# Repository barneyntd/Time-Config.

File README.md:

Time & Config.
==============

Time & Config. is a project to add a real-time clock and a configuration memory to a BBC microcomputer model B, giving
it some of the features of the BBC master. It has three main parts:
1.  A PCB containing a PCF2123 RTC, an FM25040B FRAM and an LTC4054 Li charger.
	This is designed to share a user port with a turbo-MMC card, but can also be used alone.
2.  A sideways ROM which implements:
	- OSBYTE 161 & 162: read and write NVRAM
	- OSWORD 14 & 15: read and set real-time clock
	- ROM service calls 40 & 41: extendable CONFIGURE & STATUS
	- \*-commands: TIME, CONFIGURE, STATUS, UNPLUG, INSERT & ROMS
	- configure terms: BAUD, BOOT, NOBOOT, CAPS, NOCAPS, SHCAPS, DATA, DELAY, FDRIVE, FILE, IGNORE, LANG, LOUD, QUIET, MODE, TUBE, NOTUBE, PRINT, REPEAT, TV
 	- help terms: T&C and TIME
3.  A version of SNTP over serial which allows you to synchronise the clock to internet time, to a precision of a few centiseconds.

#### Project folders
- **kicad** This holds the schematic and pcb design, as a kicad project;
- **ROM** This holds the source for the ROM code, in beebasm format;
- **sntp** This holds the SNTPoS client program in BASIC (without line numbers) and the sntpos\_server program in POSIX C.

#### Licence
This project is licensed under creative commons licence [CC BY-NC-SA 4.0](https://creativecommons.org/licenses/by-nc-sa/4.0/).
This means that you are free to use it for any noncommercial purpose, provided you credit the copyright holder, and pass on the same conditions.
If you want to create a commercial product based on Time & Config., you must obtain a seperate licence from the copyright holder.

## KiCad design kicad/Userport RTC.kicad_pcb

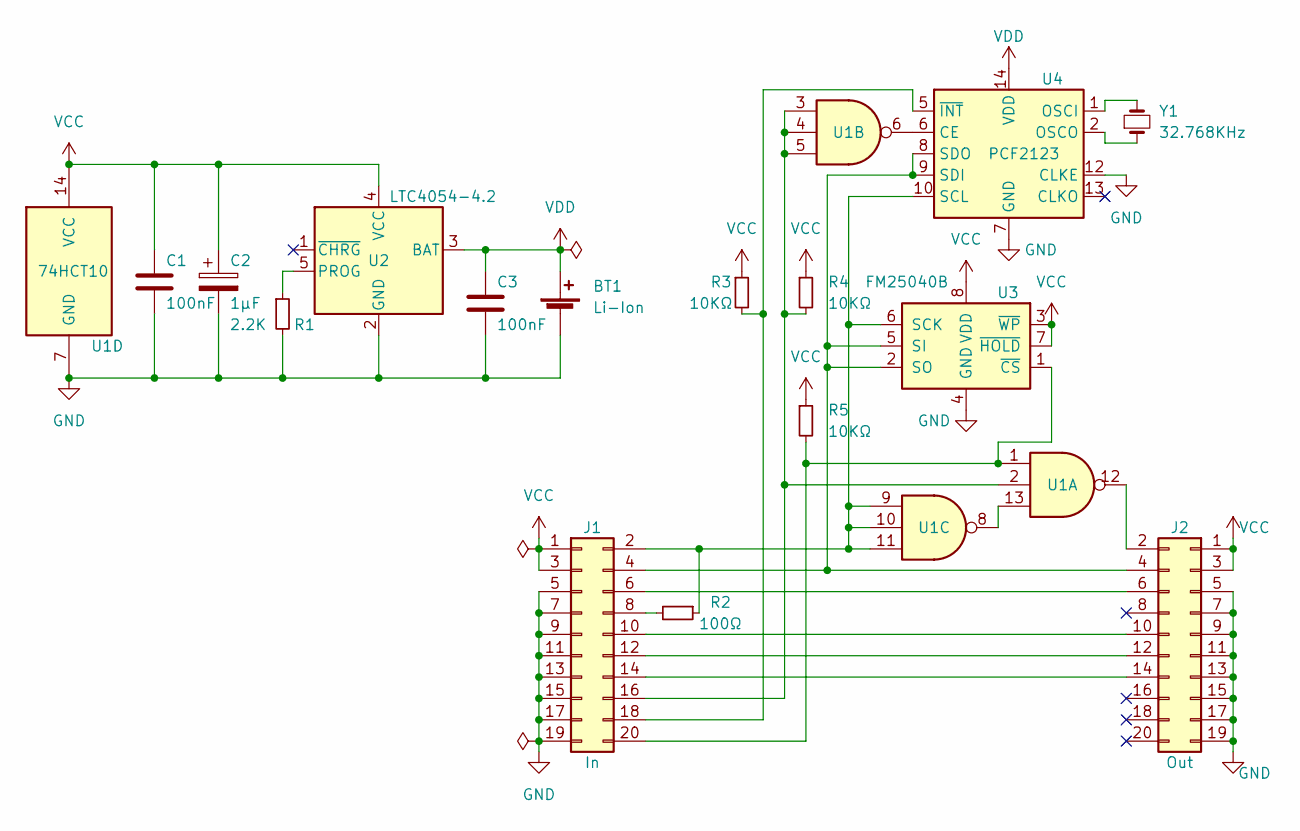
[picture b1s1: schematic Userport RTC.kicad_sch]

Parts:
BT1: Li-Ion; PinHeader_1x02_P2.54mm_Horizontal
C1, C3: 100nF; C_1206_3216Metric_Pad1.33x1.80mm_HandSolder
C2: 1µF; CP_Radial_D4.0mm_P1.50mm
J1: In; PinSocket_2x10_P2.54mm_Horizontal
J2: Out; PinHeader_2x10_P2.54mm_Reversed_Horizontal
R1: 2.2K; R_1206_3216Metric_Pad1.30x1.75mm_HandSolder
R2: 100Ω; R_1206_3216Metric_Pad1.30x1.75mm_HandSolder
R3, R4, R5: 10KΩ; R_1206_3216Metric_Pad1.30x1.75mm_HandSolder
U1: 74HCT10; SO-14_3.9x8.65mm_P1.27mm
U2: LTC4054-4.2; TSOT-23-5
U3: FM25040B; SOIC-8_3.9x4.9mm_P1.27mm
U4: PCF2123; TSSOP-14_4.4x5mm_P0.65mm
Y1: 32.768KHz; Crystal_DS26_D2.0mm_L6.0mm_Horizontal

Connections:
GND: BT1.2 (-), C1.2, C2.2, C3.2, J1.5, J1.7, J1.9, J1.11, J1.13, J1.15, J1.17, J1.19, J2.5, J2.7, J2.9, J2.11, J2.13, J2.15, J2.17, J2.19, R1.2, U1.7 (GND), U2.2 (GND), U3.4 (GND), U4.7 (GND), U4.12 (CLKE)
unnamed: J1.2, R2.1, U1.9, U1.10, U1.11, U3.6 (SCK), U4.10 (SCL)
unnamed: J1.4, J2.4, U3.2 (SO), U3.5 (SI), U4.8 (SDO), U4.9 (SDI)
unnamed: J1.6, J2.6
unnamed: J1.8, R2.2
unnamed: J1.10, J2.10
unnamed: J1.12, J2.12
unnamed: J1.14, J2.14
unnamed: J1.16, R4.2, U1.2, U1.3, U1.4, U1.5
unnamed: J1.18, R3.2, U4.5 (~INT)
unnamed: J1.20, R5.2, U1.1, U3.1 (~CS)
unnamed: J2.2, U1.12
unnamed: R1.1, U2.5 (PROG)
unnamed: U1.6, U4.6 (CE)
unnamed: U1.8, U1.13
unnamed: U4.1 (OSCI), Y1.2
unnamed: U4.2 (OSCO), Y1.1
VCC: C1.1, C2.1, J1.1, J1.3, J2.1, J2.3, R3.1, R4.1, R5.1, U1.14 (VCC), U2.4 (VCC), U3.3 (~WP), U3.7 (~HOLD), U3.8 (VDD)
VDD: BT1.1 (+), C3.1, U2.3 (BAT), U4.14 (VDD)

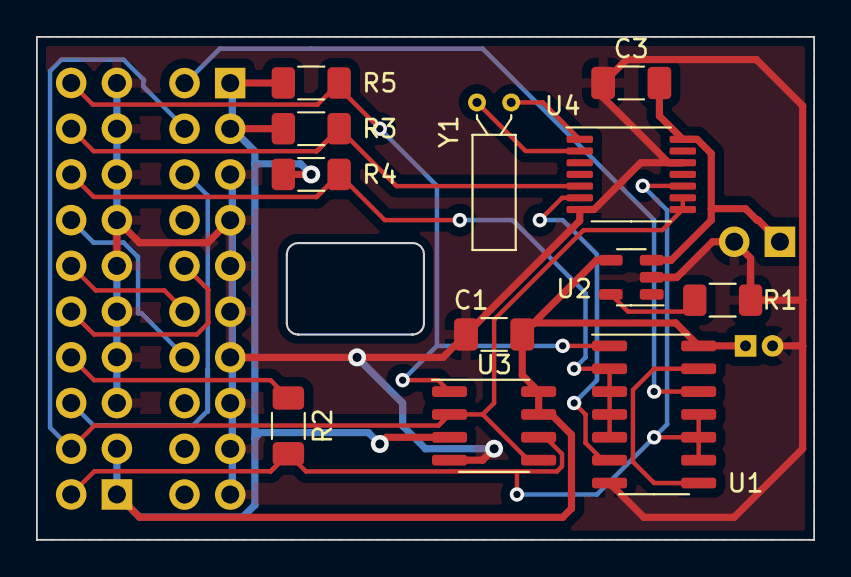
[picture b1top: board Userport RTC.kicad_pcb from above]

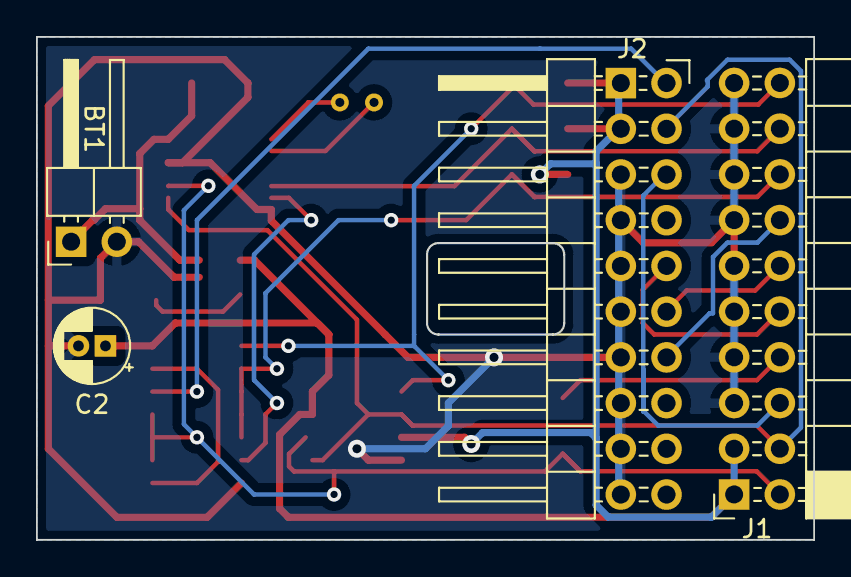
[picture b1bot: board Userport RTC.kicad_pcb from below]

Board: 2 copper layers, 43.2 x 27.9 mm, 16 parts (4 on the bottom side), 19 nets.

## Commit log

2024-03-23 Initial commit of version 0.2
2024-03-23 Added support for callibration and times saved in FRAM
2024-03-29 branching
2024-03-29 alarm test
2024-03-29 Move Alarm stuff to branch
2024-12-10 - Added lots more timezone TLAs - Changed OSWORD &0E: 5: read century & timezone 7: deleted
2024-12-11 retrieving edits from branch
2024-12-13 Final bugfix of time before adding *CONFIGURE etc
2024-12-19 First complete implementation of CONFIGURE & HELP
2025-01-02 bugfixes before experimental help simplification
2025-01-02 simplified help
2025-01-11 First complete version of configure, status, unplug, roms
2025-01-16 SNTPoS working, with server connection to sntp server
2025-01-17 Rewrote S+/-ss.cc and time arithmetic to allow -99 < ss.cc < 99
2025-01-17 Added README and LICENCE for first public release
2025-01-18 fixed a couple of minor bugs
2025-01-20 Fixed minor issues & added -l & -t to sntpos_server
2025-01-22 Changing branch
2025-01-22 tweaked .gitignore
2025-01-26 Added minute level timezones, and bumped version number to 0.03
2025-01-27 Some bugfixes and code tidying before the push
2025-01-29 Minor fixes to sntpos
2025-01-30 switch to main
2025-01-30 Some bugfixes, and support for OSWORD 14,9 & 14,10
2025-01-30 bugfix & turned off OSWORD 14,9 & 14,10 switch
2025-02-04 Added support for user-defined timezones
2025-02-06 Tidying up error numbers
2025-02-18 A few bug fixes
2025-02-22 Basic implementation done (except CONFIG parser)
2025-03-03 Implemented Configure & Status for FS & PS
2025-03-04 FS & PS only appear if NFS rom is enabled
2025-03-04 got *config FS & PS working properly
2025-03-13 Fixed startup key & unplug bugs.
2025-03-20 Changed extension to .asm, and separated rom header from root file
2025-04-24 Added SWRAM detection to *ROMS
